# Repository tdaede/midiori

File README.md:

# Installation

1. Remove a cover plate from a free x68000 expansion slot.
2. Slide card into expansion plate until it seats. It will take some force.
3. Install 3d printed cover plate.
4. Attach OUT connector to MIDI in of your synthesizer.
5. (optional) Run LINE OUT from the x68000 to the LINE IN of your synthesizer's internal mixer.

# Compatibility

A list of tested games is available [here](docs/GAMES.md).

# Changelog

See [here](docs/CHANGELOG.md).

# Differences from midiori v1

- MIDI IN and THRU ports are not implemented.
- FIFO-Rx and FIFO-IRx are not implemented.
- FIFO-ITx start/stop/clock messages are not implemented.
- SYNC and CLICK are not implemented.
- Sequencer is not implemented.
- GPIO is not implemented.
- Address is locked to 0xeafa00.
- IRQ is locked to slot+2.
- Baud rate is locked to 31250 bps, 8n1.
- 32-byte, null terminated version string, readable by writing
  the index (0-31) to 0xF4 and reading the current byte from 0xF5.
- 68k bus is implemented natively and timings are generally faster.

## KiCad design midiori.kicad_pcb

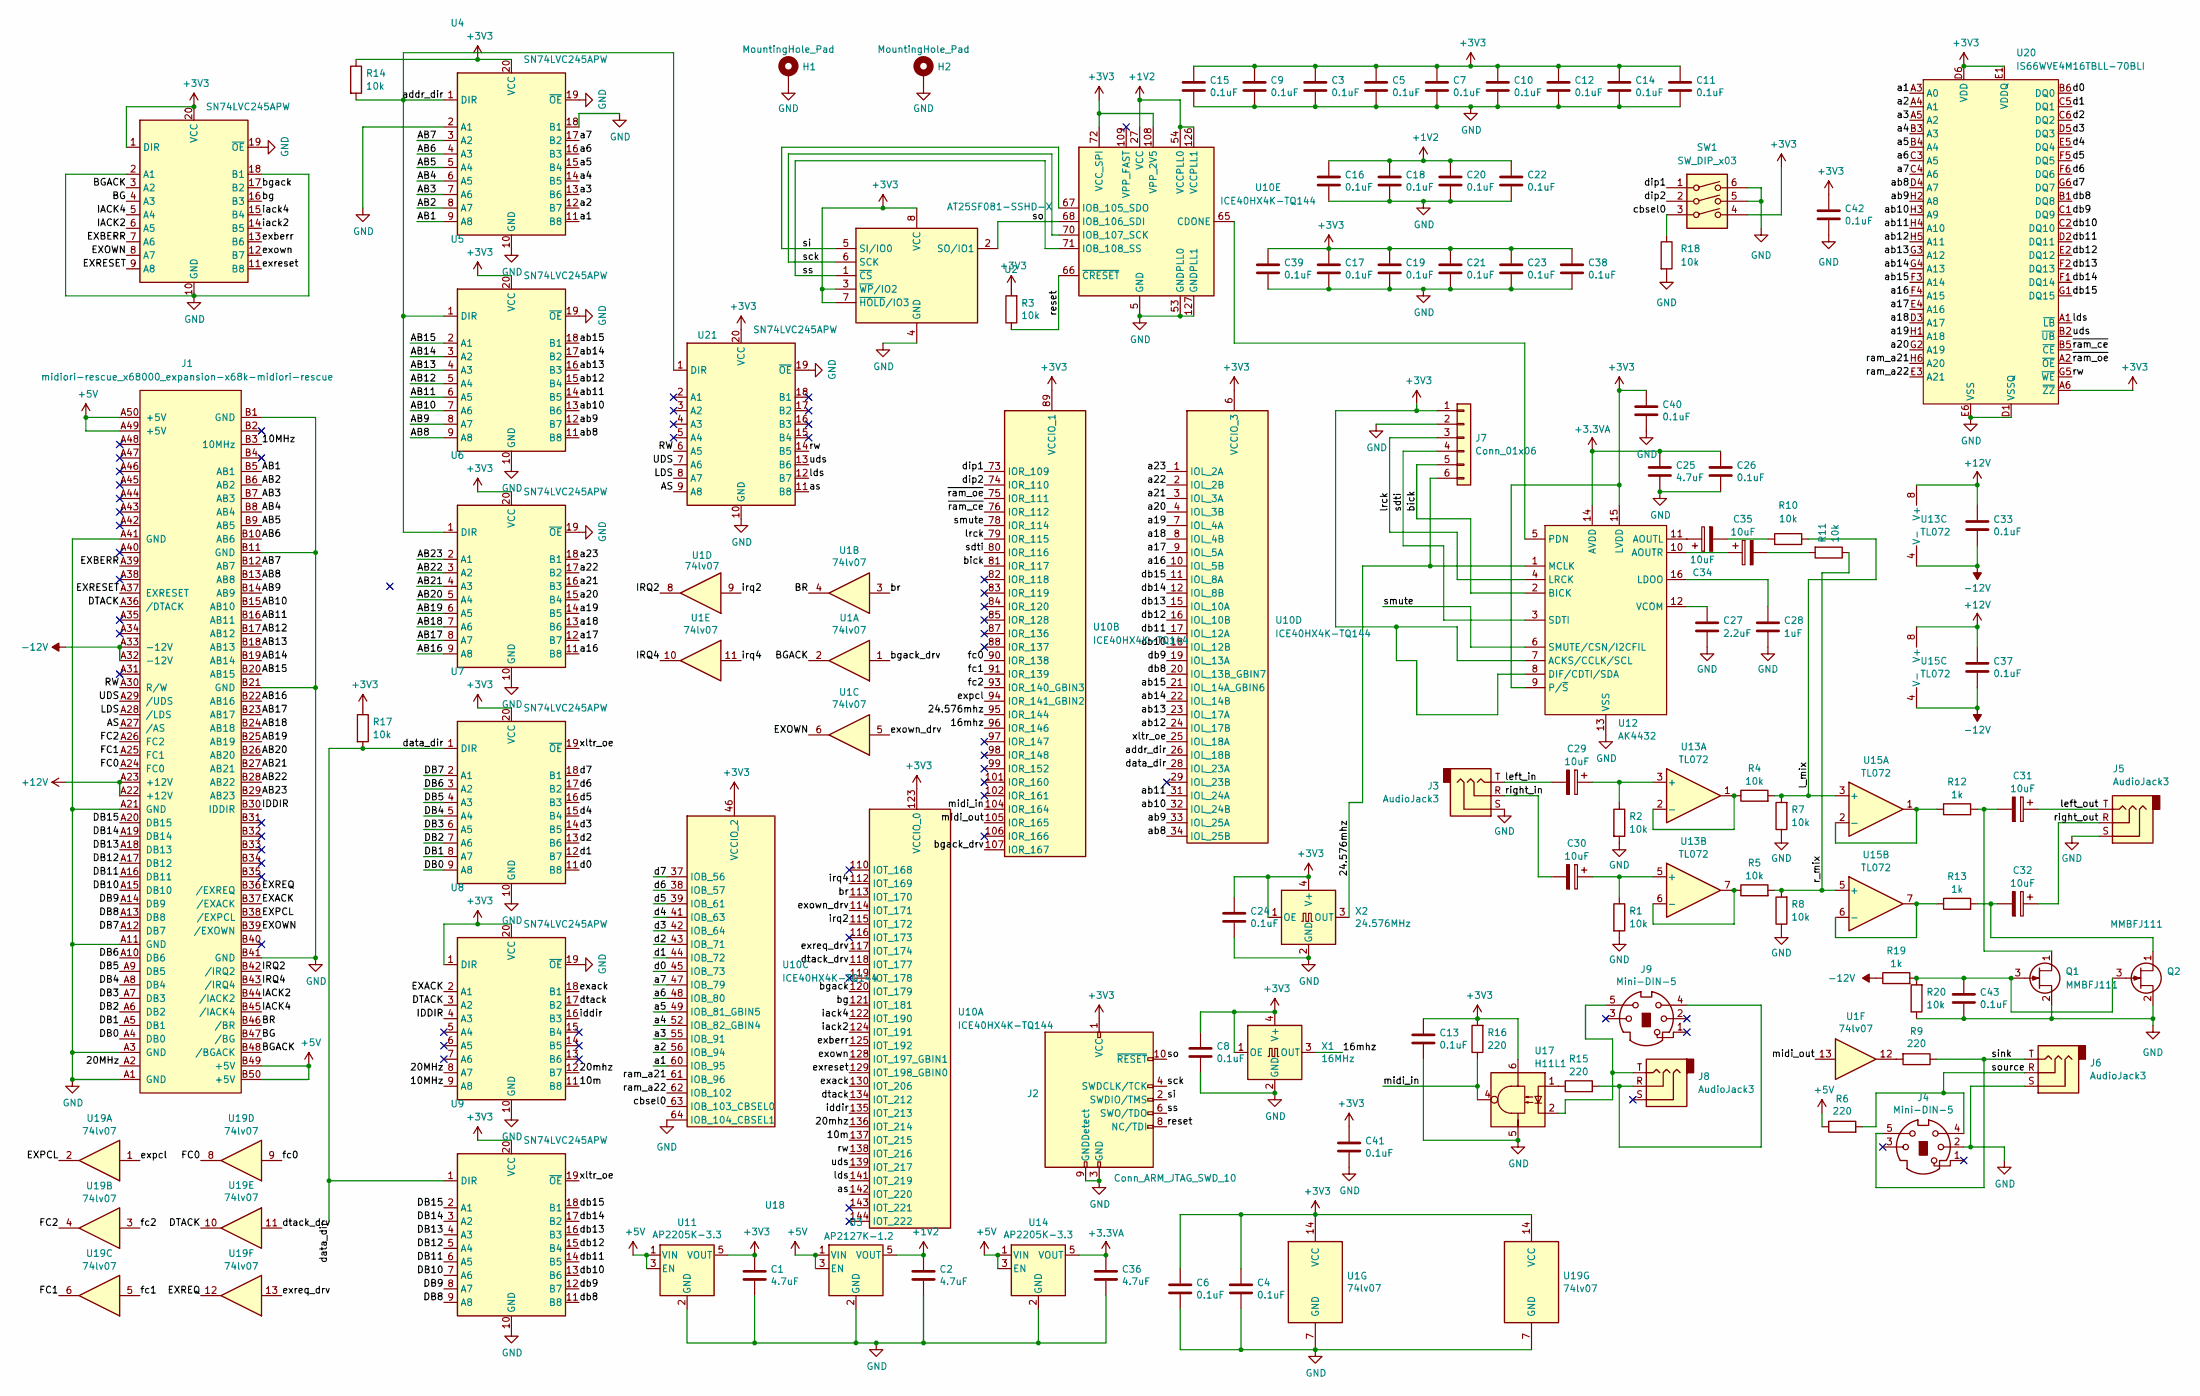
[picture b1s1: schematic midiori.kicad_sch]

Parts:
C1, C2, C25, C36: 4.7uF; C_0805_2012Metric; Digikey 490-14466-1-ND
C3, C4, C5, C6, C7, C8, C9, C10, C11, C12, C13, C14, C15, C16, C17, C18, C19, C20, C21, C22, C23, C24, C26, C33, C37, C38, C39, C40, C41, C42, C43: 0.1uF; C_0805_2012Metric; Digikey 311-1140-1-ND
C27: 2.2uF; C_0805_2012Metric; Digikey 490-14467-1-ND
C28: 1uF; C_0805_2012Metric; Digikey 311-1365-1-ND
C29, C30, C31, C32, C34, C35: 10uF; C_Elec_5x5.8; Digikey 565-HHXD350ARA220ME61GCT-ND
H1, H2: MountingHole_Pad; MountingHole_3.2mm_M3_Pad
J1: midiori-rescue_x68000_expansion-x68k-midiori-resc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; x68000_expansion_vias
J2: Conn_ARM_JTAG_SWD_10; PinHeader_2x05_P1.27mm_Vertical_SMD
J3, J5, J6, J8: AudioJack3; Jack_3.5mm_CUI_SJ1-3533NG_Horizontal; Digikey CP1-3533NG-ND
J4, J9: Mini-DIN-5; MD-50SM; Digikey CP-2250-ND
J7: Conn_01x06; PinHeader_1x06_P2.54mm_Vertical
Q1, Q2: MMBFJ111; SOT-23
R1, R2, R3, R4, R5, R7, R8, R10, R11, R14, R17, R20: 10k; R_0805_2012Metric; Digikey 311-10.0KCRCT-ND
R6, R9, R15, R16: 220; R_0805_2012Metric; Digikey 311-220CRCT-ND
R12, R13, R19: 1k; R_0805_2012Metric; Digikey 311-1.00KCRCT-ND
R18: 10k
SW1: SW_DIP_x03; SW_DIP_SPSTx03_Slide_9.78x9.8mm_W8.61mm_P2.54mm
U1, U19: 74lv07; SOIC-14_3.9x8.7mm_P1.27mm; Digikey 74LV07AS14-13DICT-ND
U2: AT25SF081-SSHD-X; SOIC-8_3.9x4.9mm_P1.27mm; Digikey AT25SF081B-SSHD-B
U3: AP2127K-1.2; SOT-23-5; Digikey AP2127K-1.2TRG1DICT-ND
U4, U5, U6, U7, U8, U9, U18, U21: SN74LVC245APW; SOIC-20W_7.5x12.8mm_P1.27mm; Digikey 1727-3104-1-ND
U10: ICE40HX4K-TQ144; TQFP-144_20x20mm_P0.5mm
U11, U14: AP2205K-3.3; SOT-23-5; Digikey AP2202K-3.3TRG1DICT-ND
U12: AK4432; TSSOP-16_4.4x5mm_P0.65mm; Digikey 974-1078-1-ND
U13, U15: TL072; SOIC-8_3.9x4.9mm_P1.27mm; Digikey 497-2200-1-ND
U17: H11L1; SMDIP-6_W9.53mm; Digikey H11L1SR2MCT-ND
U20: IS66WVE4M16TBLL-70BLI; TFBGA-48_6x10mm_Layout6x8_P0.75mm
X1: 16MHz; Oscillator_SMD_SeikoEpson_SG8002CA-4Pin_7.0x5.0mm; Digikey 110-CB3LV-3C-16M000000CT-ND
X2: 24.576MHz; Oscillator_SMD_SeikoEpson_SG8002CA-4Pin_7.0x5.0mm; Digikey 110-CB3LV-3I-24M576000CT-ND

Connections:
+1V2: C2.1, C16.1, C18.1, C20.1, C22.1, U3.5 (VOUT), U10.27 (VCC), U10.40 (VCC), U10.54 (VCCPLL0), U10.92 (VCC), U10.111 (VCC), U10.126 (VCCPLL1)
+3.3VA: C25.1, C26.1, C36.1, U12.14 (AVDD), U14.5 (VOUT)
+3V3: C1.1, C3.1, C4.1, C5.1, C6.1, C7.1, C8.1, C9.1, C10.1, C11.1, C12.1, C13.1, C14.1, C15.1, C17.1, C19.1, C21.1, C23.1, C24.1, C38.1, C39.1, C40.1, C41.1, C42.1, J2.1 (VCC), J7.1, R3.2, R14.1, R16.2, R17.1, SW1.4, U1.14 (VCC), U2.3 (~WP/IO2), U2.7 (~HOLD/IO3), U2.8 (VCC), U4.20 (VCC), U5.20 (VCC), U6.20 (VCC), U7.20 (VCC), U8.1 (DIR), U8.20 (VCC), U9.20 (VCC), U10.6 (VCCIO_3), U10.30 (VCCIO_3), U10.46 (VCCIO_2), U10.57 (VCCIO_2), U10.72 (VCC_SPI), U10.89 (VCCIO_1), U10.100 (VCCIO_1), U10.108 (VPP_2V5), U10.123 (VCCIO_0), U10.131 (VCCIO_0), U11.5 (VOUT), U12.7 (ACKS/CCLK/SCL), U12.8 (DIF/CDTI/SDA), U12.9 (P/~S), U12.15 (LVDD), U17.6, U18.1 (DIR), U18.20 (VCC), U19.14 (VCC), U20.A6 (~ZZ), U20.D6 (VDD), U20.E1 (VDDQ), U21.20 (VCC), X1.1 (OE), X1.4 (V+), X2.1 (OE), X2.4 (V+)
+5V: J1.A49 (+5V), J1.A50 (+5V), J1.B49 (+5V), J1.B50 (+5V), R6.1, U3.1 (VIN), U3.3 (EN), U11.1 (VIN), U11.3 (EN), U14.1 (VIN), U14.3 (EN)
+12V: C33.1, C37.1, J1.A22 (+12V), J1.A23 (+12V), U13.8 (V+), U15.8 (V+)
-12V: C33.2, C37.2, J1.A32 (-12V), J1.A33 (-12V), R19.1, U13.4 (V-), U15.4 (V-)
/10MHz: J1.B3 (10MHz), U8.9 (A8)
/10m: U8.11 (B8), U10.137 (IOT_215)
/16mhz: U10.96 (IOR_146), X1.3 (OUT)
/20MHz: J1.A2, U8.8 (A7)
/20mhz: U8.12 (B7), U10.136 (IOT_214)
/24.576mhz: J7.6, U10.95 (IOR_144), U12.1 (MCLK), X2.3 (OUT)
/AB1: J1.B5 (AB1), U4.9 (A8)
/AB2: J1.B6 (AB2), U4.8 (A7)
/AB3: J1.B7 (AB3), U4.7 (A6)
/AB4: J1.B8 (AB4), U4.6 (A5)
/AB5: J1.B9 (AB5), U4.5 (A4)
/AB6: J1.B10 (AB6), U4.4 (A3)
/AB7: J1.B12 (AB7), U4.3 (A2)
/AB8: J1.B13 (AB8), U5.9 (A8)
/AB9: J1.B14 (AB9), U5.8 (A7)
/AB10: J1.B15 (AB10), U5.7 (A6)
/AB11: J1.B16 (AB11), U5.6 (A5)
/AB12: J1.B17 (AB12), U5.5 (A4)
/AB13: J1.B18 (AB13), U5.4 (A3)
/AB14: J1.B19 (AB14), U5.3 (A2)
/AB15: J1.B20 (AB15), U5.2 (A1)
/AB16: J1.B22 (AB16), U6.9 (A8)
/AB17: J1.B23 (AB17), U6.8 (A7)
/AB18: J1.B24 (AB18), U6.7 (A6)
/AB19: J1.B25 (AB19), U6.6 (A5)
/AB20: J1.B26 (AB20), U6.5 (A4)
/AB21: J1.B27 (AB21), U6.4 (A3)
/AB22: J1.B28 (AB22), U6.3 (A2)
/AB23: J1.B29 (AB23), U6.2 (A1)
/AS: J1.A27 (/AS), U21.9 (A8)
/BG: J1.B47 (/BG), U18.4 (A3)
/BGACK: J1.B48 (/BGACK), U1.2, U18.3 (A2)
/BR: J1.B46 (/BR), U1.4
/DB0: J1.A4 (DB0), U7.9 (A8)
/DB1: J1.A5 (DB1), U7.8 (A7)
/DB2: J1.A6 (DB2), U7.7 (A6)
/DB3: J1.A7 (DB3), U7.6 (A5)
/DB4: J1.A8 (DB4), U7.5 (A4)
/DB5: J1.A9 (DB5), U7.4 (A3)
/DB6: J1.A10 (DB6), U7.3 (A2)
/DB7: J1.A12 (DB7), U7.2 (A1)
/DB8: J1.A13 (DB8), U9.9 (A8)
/DB9: J1.A14 (DB9), U9.8 (A7)
/DB10: J1.A15 (DB10), U9.7 (A6)
/DB11: J1.A16 (DB11), U9.6 (A5)
/DB12: J1.A17 (DB12), U9.5 (A4)
/DB13: J1.A18 (DB13), U9.4 (A3)
/DB14: J1.A19 (DB14), U9.3 (A2)
/DB15: J1.A20 (DB15), U9.2 (A1)
/DTACK: J1.A36 (/DTACK), U8.3 (A2), U19.10
/EXACK: J1.B37 (/EXACK), U8.2 (A1)
/EXBERR: J1.A39, U18.7 (A6)
/EXOWN: J1.B39 (/EXOWN), U1.6, U18.8 (A7)
/EXPCL: J1.B38 (/EXPCL), U19.2
/EXREQ: J1.B36 (/EXREQ), U19.12
/EXRESET: J1.A37 (EXRESET), U18.9 (A8)
/FC0: J1.A24 (FC0), U19.8
/FC1: J1.A25 (FC1), U19.6
/FC2: J1.A26 (FC2), U19.4
/IACK2: J1.B44 (/IACK2), U18.6 (A5)
/IACK4: J1.B45 (/IACK4), U18.5 (A4)
/IDDIR: J1.B30 (IDDIR), U8.4 (A3)
/IRQ2: J1.B42 (/IRQ2), U1.8
/IRQ4: J1.B43 (/IRQ4), U1.10
/LDS: J1.A28 (/LDS), U21.8 (A7)
/RW: J1.A30 (R/W), U21.6 (A5)
/UDS: J1.A29 (/UDS), U21.7 (A6)
/a1: U4.11 (B8), U10.60 (IOB_95), U20.A3 (A0)
/a2: U4.12 (B7), U10.56 (IOB_94), U20.A4 (A1)
/a3: U4.13 (B6), U10.55 (IOB_91), U20.A5 (A2)
/a4: U4.14 (B5), U10.52 (IOB_82_GBIN4), U20.B3 (A3)
/a5: U4.15 (B4), U10.49 (IOB_81_GBIN5), U20.B4 (A4)
/a6: U4.16 (B3), U10.48 (IOB_80), U20.C3 (A5)
/a7: U4.17 (B2), U10.47 (IOB_79), U20.C4 (A6)
/a16: U6.11 (B8), U10.10 (IOL_5B), U20.F4 (A15)
/a17: U6.12 (B7), U10.9 (IOL_5A), U20.E4 (A16)
/a18: U6.13 (B6), U10.8 (IOL_4B), U20.D3 (A17)
/a19: U6.14 (B5), U10.7 (IOL_4A), U20.H1 (A18)
/a20: U6.15 (B4), U10.4 (IOL_3B), U20.G2 (A19)
/a21: U6.16 (B3), U10.3 (IOL_3A)
/a22: U6.17 (B2), U10.2 (IOL_2B)
/a23: U6.18 (B1), U10.1 (IOL_2A)
/ab8: U5.11 (B8), U10.34 (IOL_25B), U20.D4 (A7)
/ab9: U5.12 (B7), U10.33 (IOL_25A), U20.H2 (A8)
/ab10: U5.13 (B6), U10.32 (IOL_24B), U20.H3 (A9)
/ab11: U5.14 (B5), U10.31 (IOL_24A), U20.H4 (A10)
/ab12: U5.15 (B4), U10.24 (IOL_17B), U20.H5 (A11)
/ab13: U5.16 (B3), U10.23 (IOL_17A), U20.G3 (A12)
/ab14: U5.17 (B2), U10.22 (IOL_14B), U20.G4 (A13)
/ab15: U5.18 (B1), U10.21 (IOL_14A_GBIN6), U20.F3 (A14)
/addr_dir: R14.2, U4.1 (DIR), U5.1 (DIR), U6.1 (DIR), U10.26 (IOL_18B), U21.1 (DIR)
/as: U10.142 (IOT_220), U21.11 (B8)
/bg: U10.121 (IOT_181), U18.16 (B3)
/bgack: U10.120 (IOT_179), U18.17 (B2)
/bgack_drv: U1.1, U10.107 (IOR_167)
/bick: J7.5, U10.81 (IOR_117), U12.2 (BICK)
/br: U1.3, U10.113 (IOT_170)
/cbsel0: R18.1, SW1.3, U10.63 (IOB_103_CBSEL0)
/d0: U7.11 (B8), U10.45 (IOB_73), U20.B6 (DQ0)
/d1: U7.12 (B7), U10.44 (IOB_72), U20.C5 (DQ1)
/d2: U7.13 (B6), U10.43 (IOB_71), U20.C6 (DQ2)
/d3: U7.14 (B5), U10.42 (IOB_64), U20.D5 (DQ3)
/d4: U7.15 (B4), U10.41 (IOB_63), U20.E5 (DQ4)
/d5: U7.16 (B3), U10.39 (IOB_61), U20.F5 (DQ5)
/d6: U7.17 (B2), U10.38 (IOB_57), U20.F6 (DQ6)
/d7: U7.18 (B1), U10.37 (IOB_56), U20.G6 (DQ7)
/data_dir: R17.2, U7.1 (DIR), U9.1 (DIR), U10.28 (IOL_23A)
/db8: U9.11 (B8), U10.20 (IOL_13B_GBIN7), U20.B1 (DQ8)
/db9: U9.12 (B7), U10.19 (IOL_13A), U20.C1 (DQ9)
/db10: U9.13 (B6), U10.18 (IOL_12B), U20.C2 (DQ10)
/db11: U9.14 (B5), U10.17 (IOL_12A), U20.D2 (DQ11)
/db12: U9.15 (B4), U10.16 (IOL_10B), U20.E2 (DQ12)
/db13: U9.16 (B3), U10.15 (IOL_10A), U20.F2 (DQ13)
/db14: U9.17 (B2), U10.12 (IOL_8B), U20.F1 (DQ14)
/db15: U9.18 (B1), U10.11 (IOL_8A), U20.G1 (DQ15)
/dip1: SW1.1, U10.73 (IOR_109)
/dip2: SW1.2, U10.74 (IOR_110)
/dtack: U8.17 (B2), U10.134 (IOT_212)
/dtack_drv: U10.118 (IOT_177), U19.11
/exack: U8.18 (B1), U10.130 (IOT_206)
/exberr: U10.125 (IOT_192), U18.13 (B6)
/exown: U10.128 (IOT_197_GBIN1), U18.12 (B7)
/exown_drv: U1.5, U10.114 (IOT_171)
/expcl: U10.94 (IOR_141_GBIN2), U19.1
/exreq_drv: U10.117 (IOT_174), U19.13
/exreset: U10.129 (IOT_198_GBIN0), U18.11 (B8)
/fc0: U10.90 (IOR_138), U19.9
/fc1: U10.91 (IOR_139), U19.5
/fc2: U10.93 (IOR_140_GBIN3), U19.3
/iack2: U10.124 (IOT_191), U18.14 (B5)
/iack4: U10.122 (IOT_190), U18.15 (B4)
/iddir: U8.16 (B3), U10.135 (IOT_213)
/irq2: U1.9, U10.115 (IOT_172)
/irq4: U1.11, U10.112 (IOT_169)
/l_mix: R4.2, R7.2, R10.1, U15.3 (+)
/lds: U10.141 (IOT_219), U20.A1 (~LB), U21.12 (B7)
/left_in: C29.2, J3.T
/left_out: C31.1, J5.T
/lrck: J7.3, U10.79 (IOR_115), U12.4 (LRCK)
/midi_in: R16.1, U10.104 (IOR_164), U17.4
/midi_out: U1.13, U10.105 (IOR_165)
/r_mix: R5.2, R8.2, R11.1, U15.5 (+)
/ram_a21: U10.61 (IOB_96), U20.H6 (A20)
/ram_a22: U10.62 (IOB_102), U20.E3 (A21)
/reset: J2.8 (NC/TDI), R3.1, U10.66 (~CRESET)
/right_in: C30.2, J3.R
/right_out: C32.1, J5.R
/rw: U10.138 (IOT_216), U20.G5 (~WE), U21.14 (B5)
/sck: J2.4 (SWDCLK/TCK), U2.6 (SCK), U10.70 (IOB_107_SCK)
/sdti: J7.4, U10.80 (IOR_116), U12.3 (SDTI)
/si: J2.2 (SWDIO/TMS), U2.5 (SI/IO0), U10.67 (IOB_105_SDO)
/sink: J4.5, J6.T, R9.1
/smute: U10.78 (IOR_114), U12.6 (SMUTE/CSN/I2CFIL)
/so: J2.10 (~RESET), U2.2 (SO/IO1), U10.68 (IOB_106_SDI)
/source: J4.4, J6.R, R6.2
/ss: J2.6 (SWO/TDO), U2.1 (~CS), U10.71 (IOB_108_SS)
/uds: U10.139 (IOT_217), U20.B2 (~UB), U21.13 (B6)
/xltr_oe: U7.19 (~OE), U9.19 (~OE), U10.25 (IOL_18A)
/~ram_ce: U10.76 (IOR_112), U20.B5 (~CE)
/~ram_oe: U10.75 (IOR_111), U20.A2 (~OE)
GND: C1.2, C2.2, C3.2, C4.2, C5.2, C6.2, C7.2, C8.2, C9.2, C10.2, C11.2, C12.2, C13.2, C14.2, C15.2, C16.2, C17.2, C18.2, C19.2, C20.2, C21.2, C22.2, C23.2, C24.2, C25.2, C26.2, C27.2, C28.2, C36.2, C38.2, C39.2, C40.2, C41.2, C42.2, C43.2, H1.1 (1_1), H2.1 (1_1), J1.A1 (GND), J1.A3 (GND), J1.A11 (GND), J1.A21 (GND), J1.A41 (GND), J1.B1 (GND), J1.B11 (GND), J1.B21 (GND), J1.B41 (GND), J2.3 (GND), J2.5 (GND), J2.9 (GNDDetect), J3.S, J4.2, J5.S, J6.S, J7.2, Q1.2 (S), Q2.2 (S), R1.2, R2.2, R7.1, R8.1, R18.2, R20.1, SW1.5, SW1.6, U1.7 (GND), U2.4 (GND), U3.2 (GND), U4.2 (A1), U4.10 (GND), U4.18 (B1), U4.19 (~OE), U5.10 (GND), U5.19 (~OE), U6.10 (GND), U6.19 (~OE), U7.10 (GND), U8.10 (GND), U8.19 (~OE), U9.10 (GND), U10.5 (GND), U10.13 (GND), U10.14 (GND), U10.53 (GNDPLL0), U10.59 (GND), U10.64 (IOB_104_CBSEL1), U10.69 (GND), U10.86 (GND), U10.103 (GND), U10.127 (GNDPLL1), U10.132 (GND), U10.140 (GND), U11.2 (GND), U12.13 (VSS), U14.2 (GND), U17.5, U18.2 (A1), U18.10 (GND), U18.18 (B1), U18.19 (~OE), U19.7 (GND), U20.D1 (VSSQ), U20.E6 (VSS), U21.10 (GND), U21.19 (~OE), X1.2 (GND), X2.2 (GND)
unnamed: C34.2, R10.2
unnamed: C35.2, R11.2
unnamed: J8.R, J9.4, R15.2
unnamed: J8.T, J9.5, U17.2
unnamed: C31.2, Q1.1 (D), R12.2
unnamed: C43.1, Q1.3 (G), Q2.3 (G), R19.2, R20.2
unnamed: C32.2, Q2.1 (D), R13.2
unnamed: R9.2, U1.12
unnamed: R15.1, U17.1
unnamed: U10.65 (CDONE), U12.5 (PDN)
unnamed: C34.1, U12.11 (AOUTL)
unnamed: C35.1, U12.10 (AOUTR)
unnamed: C28.1, U12.16 (LDOO)
unnamed: C27.1, U12.12 (VCOM)
unnamed: C29.1, R2.1, U13.3 (+)
unnamed: R4.1, U13.1, U13.2 (-)
unnamed: C30.1, R1.1, U13.5 (+)
unnamed: R5.1, U13.6 (-), U13.7
unnamed: R12.1, U15.1, U15.2 (-)
unnamed: R13.1, U15.6 (-), U15.7

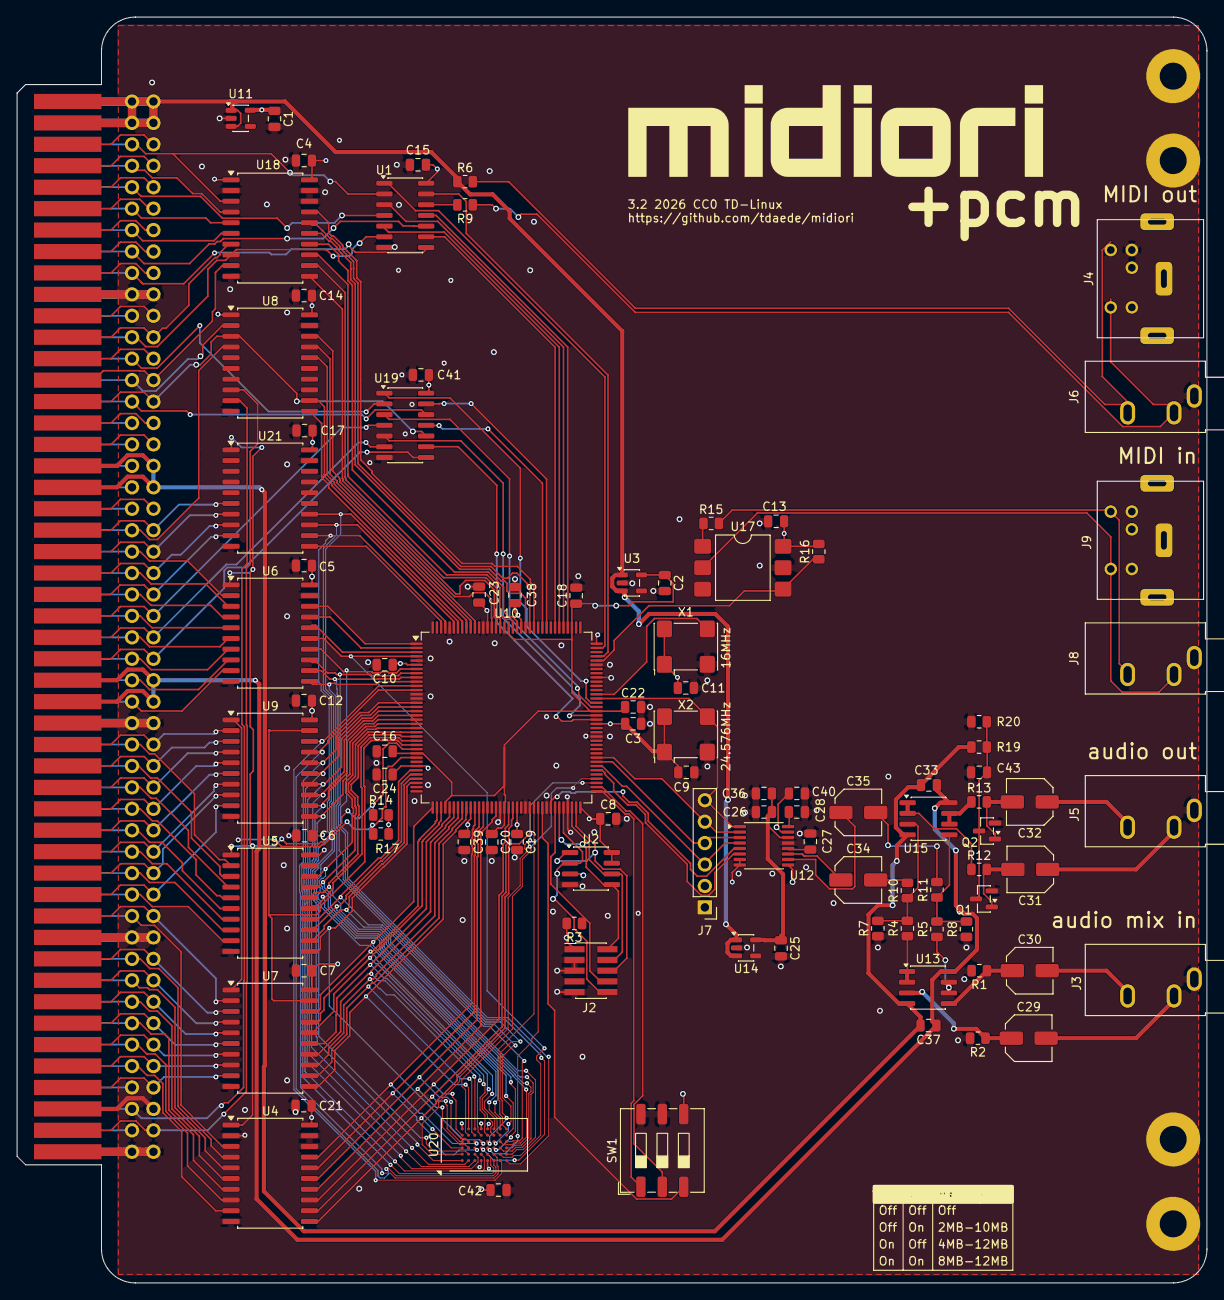
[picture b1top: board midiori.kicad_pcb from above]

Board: 4 copper layers, 141.0 x 150.0 mm, 99 parts (0 on the bottom side), 187 nets.

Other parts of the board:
svg2mod: G***; midiori_logo

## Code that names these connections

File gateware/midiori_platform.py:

from amaranth.build import *
from amaranth.vendor.lattice_ice40 import LatticeICE40Platform

__all__ = ["MidioriPlatform"]

class MidioriPlatform(LatticeICE40Platform):
    device    = "iCE40HX1K"
    package   = "vq100"
    clocks    = [
        ("sync", 16e6),
    ]
    resources = [
        Resource("sync", 0, Pins("63", dir="i"), Clock(16e6),
                 Attrs(GLOBAL=True, IO_STANDARD="SB_LVCMOS33")),
        Resource("rw", 0, Pins("100", dir="i"), Attrs(IO_STANDARD="SB_LVCMOS33")),
        Resource("exreset", 0, Pins("99", dir="i"), Attrs(IO_STANDARD="SB_LVCMOS33")),
        Resource("ioclk", 0, Pins("97", dir="i"), Attrs(IO_STANDARD="SB_LVCMOS33")),
        Resource("iddir", 0, Pins("96", dir="i"), Attrs(IO_STANDARD="SB_LVCMOS33")) ,
        Resource("iack4", 0,Pins("95", dir="i"), Attrs(IO_STANDARD="SB_LVCMOS33")),
        Resource("iack2", 0, Pins("94", dir="i"), Attrs(IO_STANDARD="SB_LVCMOS33")),
        Resource("dtack", 0, Pins("93", dir="o"), Attrs(IO_STANDARD="SB_LVCMOS33")),
        Resource("irq4", 0, Pins("91", dir="o"), Attrs(IO_STANDARD="SB_LVCMOS33")),
        Resource("irq2", 0, Pins("90", dir="o"), Attrs(IO_STANDARD="SB_LVCMOS33")),
        Resource("lds", 0, Pins("1", dir="i"), Attrs(IO_STANDARD="SB_LVCMOS33")),
        Resource("as", 0, Pins("2", dir="i"), Attrs(IO_STANDARD="SB_LVCMOS33")),
        Resource("a", 0, Pins("3", dir="i"), Attrs(IO_STANDARD="SB_LVCMOS33")),
        Resource("b", 0, Pins("4", dir="i"), Attrs(IO_STANDARD="SB_LVCMOS33")),
        Resource("c", 0, Pins("7", dir="i"), Attrs(IO_STANDARD="SB_LVCMOS33")),
        Resource("addr", 0, Pins("40 37 36 34 33 30 29 18 16 15 13 12 10 9 8 81 80 79 78 74 73 72 71", dir="i"), Attrs(IO_STANDARD="SB_LVCMOS33")),
        Resource("data", 0, Pins("28 27 26 25 24 21 20 19", dir="io"), Attrs(IO_STANDARD="SB_LVCMOS33")),
        Resource("xltr_oe", 0, Pins("51", dir="o"), Attrs(IO_STANDARD="SB_LVCMOS33")),
        Resource("tx", 0, Pins("66", dir="o"), Attrs(IO_STANDARD="SB_LVCMOS33"))
    ]
    connectors = []

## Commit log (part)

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2018-11-30 add cache
2018-11-30 finish
2018-11-30 Add footprints
2018-11-30 Add board outline
2018-12-01 Remove 74ls133 from address decoding
2018-12-18 more
2018-12-23 silkscreen improvements
2018-12-23 add logo svg
2018-12-24 ground unused inputs
2018-12-27 rev1
2019-01-20 Move IN THRU OUT labels
2019-02-02 bugfixes
2019-02-02 add license
2019-02-02 pretty up some traces
2019-02-26 Add packing label
2019-02-26 Add pulls
2019-02-26 add readme
2019-04-23 PCB layout of fpga version
2019-04-23 Add ICE40 and SN74LVC8T245 symbols
2019-04-23 route board
2019-05-24 wip gateware
2019-05-25 first working register reads
2019-05-30 Add basic tx fifo
2019-05-31 Update readme with current implementation details
2019-05-31 First partially working version
2019-06-02 Working interrupts
2019-06-03 midiori v2.1 pcb
2019-06-03 Hide J1 text
2019-06-05 PCB outline fixes
2019-06-16 Fix sck/ss on schematic
2019-06-16 set solder mask minimum width to 0
2019-06-18 Add some assertions in the simulation
2019-06-29 update packing label version
2019-07-03 add errata
2019-07-03 Add secret register to get midiori version.
2019-07-03 add compatibility list
2019-07-03 expand compatibility list
2019-07-03 fix compat list formatting
2019-07-04 update compatibility list
2019-07-13 Implement general purpose timer
2019-07-13 update readme with current impl
2019-08-20 Add midi clock counter.
    Click counter is also added but it's not wired up yet
    due to not having the isr mux.
2019-08-20 Implement selectable clkm divider.
2019-08-20 Update README for newly implemented features.
2019-08-20 more fixes
2019-08-20 Add verilog output option
2019-08-20 Fix up nmigen platform.
2019-08-20 nmigen
2019-08-20 Update device name
2019-08-22 Use PriorityEncoder for isr vector
2019-08-22 Add IC and exreset support
2019-08-22 Add BRKE function
2019-08-22 Add TXE flag
2019-08-22 Properly implement TXIDL flag
2019-08-23 Make TXIDL counter reset on non-empty or tx disable
2019-08-23 Drop unused signal
2019-08-23 Add 0xfe idle character transmission.
2019-08-23 Drop debugging comments
2019-08-23 Gate sending 0xfe on ASE register.
2019-08-23 Correct txidl period
2019-08-23 Update readme and compatibility list
2019-08-24 Update readme to include version string info
2019-08-24 Add link to compat list
2019-08-24 Add changelog.
2019-08-24 Add more details to changelog
2019-08-24 Change changelog formatting
2019-08-26 Fix packing label port names
2019-08-26 Add back plate mechanical files
2019-08-27 Add Deadly Edge to compatibility list
2019-08-28 Add Bleed Out to compatibility list
2020-02-24 update zones
2020-02-24 add more connectors
2020-02-24 one connector
2020-02-24 some changes
2020-02-24 more improvements
2020-02-24 always use long git describe output
2020-03-06 Update packing label
2020-03-06 Fix packing label font
2020-03-06 add QR code to packing label
2020-03-06 Drop white bg from qr code
2020-03-06 align text
2020-03-13 fix qr code on packing label
2020-05-18 Add minidin plate
2020-07-16 add granada to working list
2020-11-06 Add names to X68K exp conn
2020-11-06 A1..50 translated
2020-11-06 Complete b-side of expansion pinout
2020-11-06 Remove screenshot of Outside X68000
2022-02-05 Add names to X68K expansion connector symbol (#2)
    * Add names to X68K exp conn
    * A1..50 translated
    * Complete b-side of expansion pinout
    * Remove screenshot of Outside X68000
2024-11-20 extremely basic port to amaranth 0.4
2024-11-20 rename some deprecated fields
2024-11-20 update UART to Elaboratable
2024-11-23 rename ice40 device
2024-11-24 update to amaranth style
2024-12-04 Add i2s audio circuit.
2024-12-04 fix some electrical rule checker errors
2024-12-06 small schematic changes
2024-12-06 convert pcb version
2024-12-07 switch to single psu translator
2024-12-09 add bus mastering and midi in
2024-12-09 aaaaaaaaaaa
2024-12-10 swap optos
2024-12-10 crystal swap
2024-12-10 missing wire
2024-12-10 drc fixes
2024-12-10 some extra test pads
2024-12-10 fix board edge clearances
2024-12-11 v3.0
2024-12-11 add bom
2024-12-11 lvc245
2024-12-13 add oscillator 3d model
2025-10-03 add expcl/fc0/fc1/fc2, fix audio power
2025-10-03 generate 3.1
2026-06-24 add bgack readback pin

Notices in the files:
midiori.kicad_pcb:
3.2 2026 CC0 TD-Linux
